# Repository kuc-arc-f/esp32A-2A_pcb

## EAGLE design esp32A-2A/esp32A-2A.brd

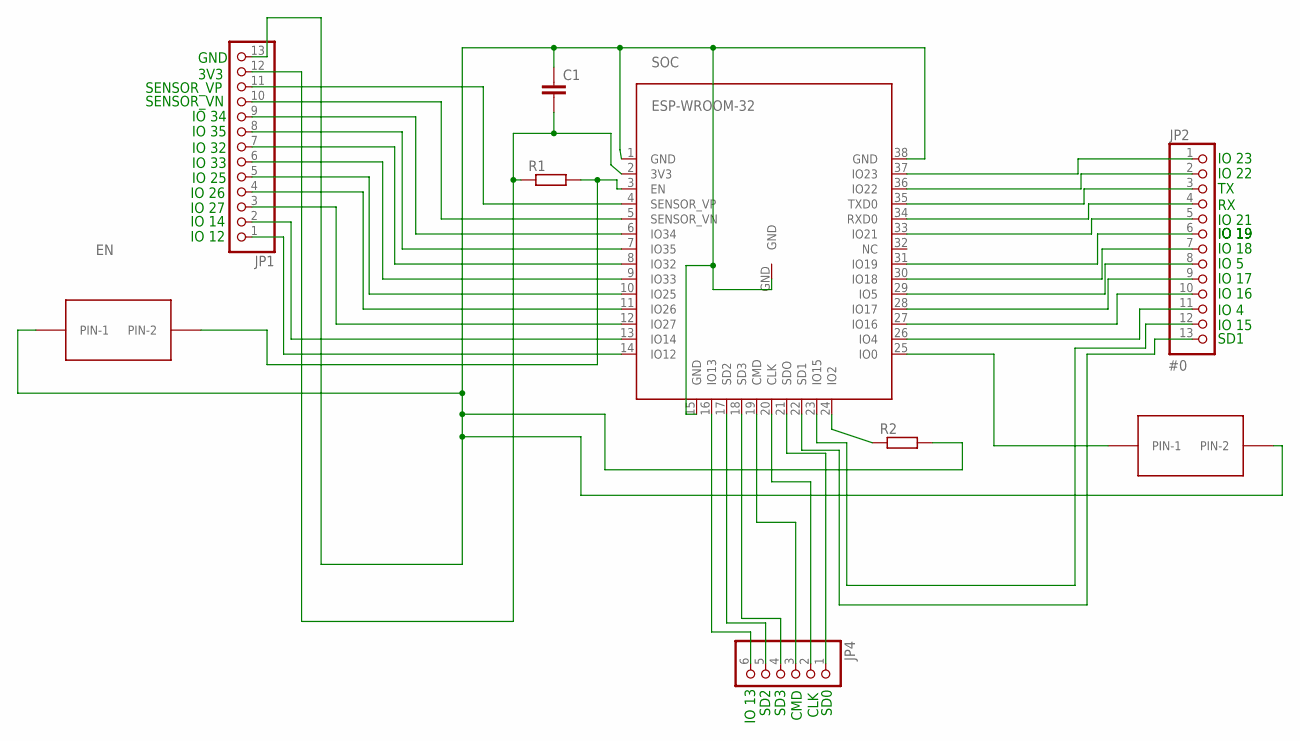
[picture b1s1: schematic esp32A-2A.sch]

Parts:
#0: BTN2-EX; B3F-10XX
C1: C-EUC0603; C0603
EN: BTN2-EX; B3F-10XX
JP1, JP2: PINHD-1X13; 1X13
JP4: PINHD-1X6; 1X06
R1, R2: R-EU_R0603; R0603
SOC: ESP-WROOM-32

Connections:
unnamed: JP2.2, SOC.36 (IO22)
unnamed: #0.1 (PIN-1), SOC.25 (IO0)
unnamed: R2.1, SOC.24 (IO2)
unnamed: EN.2 (PIN-2), R1.2, SOC.3 (EN)
unnamed: JP2.3, SOC.35 (TXD0)
unnamed: JP2.4, SOC.34 (RXD0)
unnamed: JP1.11, SOC.4 (SENSOR_VP)
unnamed: JP2.1, SOC.37 (IO23)
unnamed: JP4.6, SOC.16 (IO13)
unnamed: JP4.2, SOC.20 (CLK)
unnamed: JP2.5, SOC.33 (IO21)
unnamed: C1.2, JP1.12, R1.1, SOC.2 (3V3)
unnamed: #0.2 (PIN-2), C1.1, EN.1 (PIN-1), JP1.13, R2.2, SOC.1 (GND), SOC.15 (GND), SOC.38 (GND), SOC.GND
unnamed: JP2.6, SOC.31 (IO19)
unnamed: JP2.7, SOC.30 (IO18)
unnamed: JP2.8, SOC.29 (IO5)
unnamed: JP2.9, SOC.28 (IO17)
unnamed: JP2.10, SOC.27 (IO16)
unnamed: JP2.11, SOC.26 (IO4)
unnamed: JP1.10, SOC.5 (SENSOR_VN)
unnamed: JP1.9, SOC.6 (IO34)
unnamed: JP1.8, SOC.7 (IO35)
unnamed: JP1.7, SOC.8 (IO32)
unnamed: JP1.6, SOC.9 (IO33)
unnamed: JP1.5, SOC.10 (IO25)
unnamed: JP1.4, SOC.11 (IO26)
unnamed: JP1.3, SOC.12 (IO27)
unnamed: JP4.1, SOC.21 (SDO)
unnamed: JP2.13, SOC.22 (SD1)
unnamed: JP2.12, SOC.23 (IO15)
unnamed: JP4.3, SOC.19 (CMD)
unnamed: JP4.4, SOC.18 (SD3)
unnamed: JP4.5, SOC.17 (SD2)
unnamed: JP1.2, SOC.13 (IO14)
unnamed: JP1.1, SOC.14 (IO12)

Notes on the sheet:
GND
3V3
IO 23
IO 22
IO 21
SENSOR_VP
SENSOR_VN
IO 34
IO 12
IO 14
IO 27
IO 26
IO 35
IO 32
IO 33
IO 25
IO 19
IO 18
IO 5
IO 17
IO 16
IO 4
IO 15
SD1
IO 13
SD2
SD3
CMD
CLK
SD0

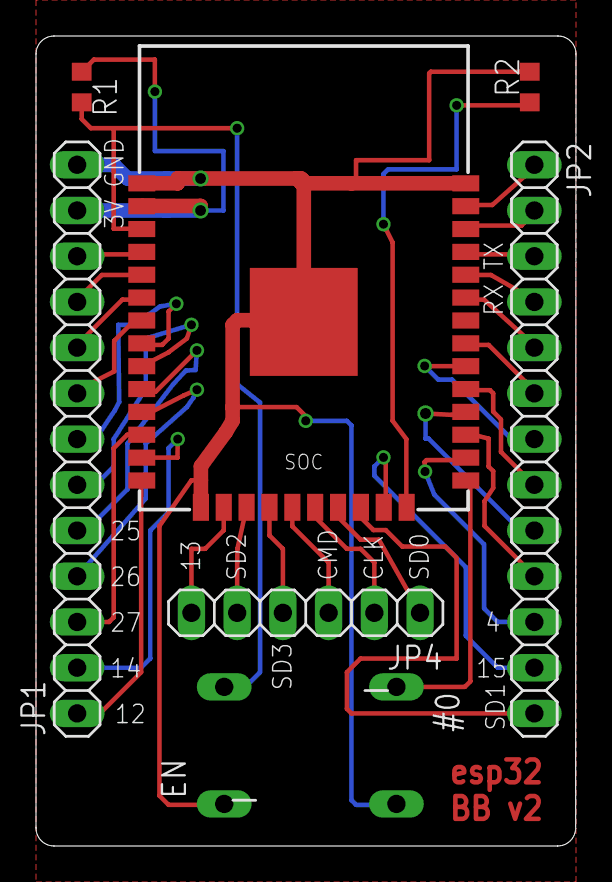
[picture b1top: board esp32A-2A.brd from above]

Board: 2 copper layers, 30.0 x 45.0 mm, 9 parts (1 on the bottom side), 35 nets.

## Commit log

2017-08-20 new, 08-20a1
